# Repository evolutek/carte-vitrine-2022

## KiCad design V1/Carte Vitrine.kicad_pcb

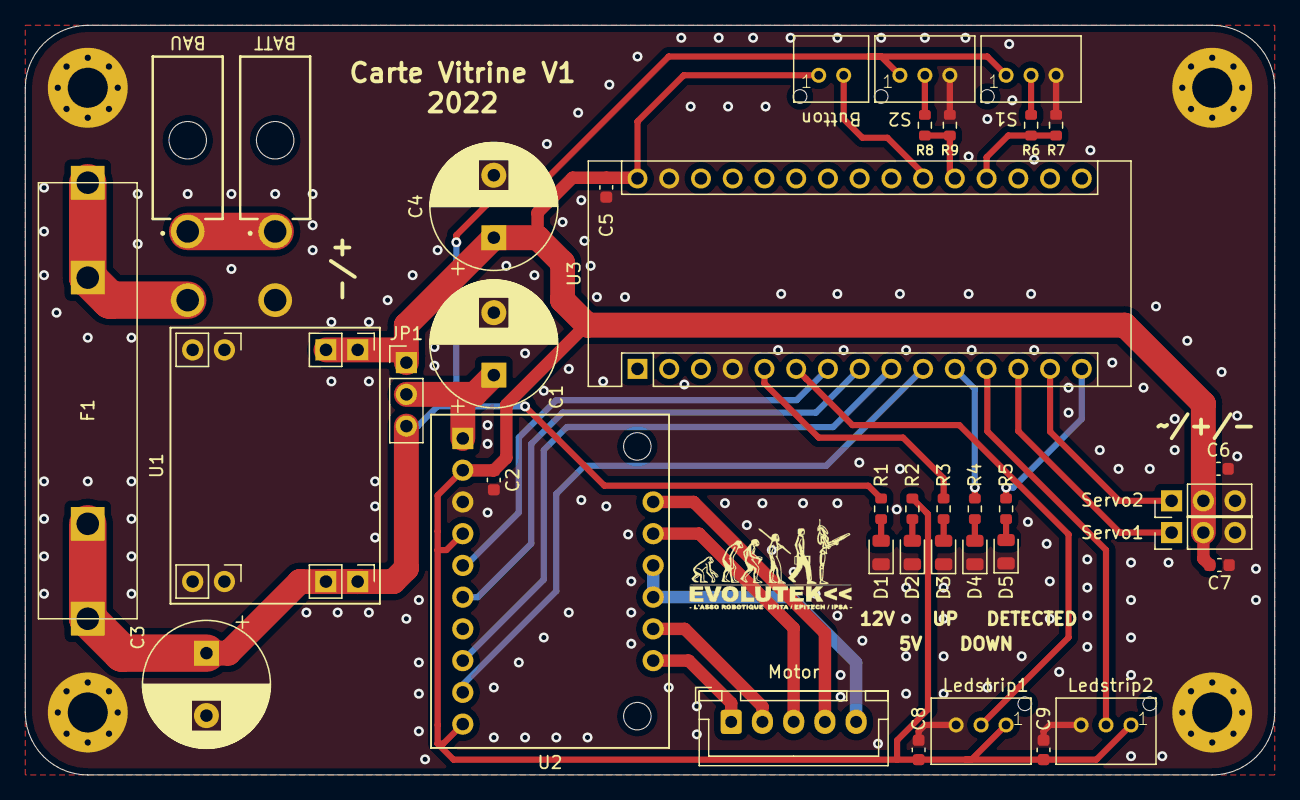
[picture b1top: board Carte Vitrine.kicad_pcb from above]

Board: 2 copper layers, 100.0 x 60.0 mm, 42 parts (0 on the bottom side), 32 nets.

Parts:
BATT: Conn_01x02_Male; 649002227222
BAU: Conn_01x02_Male; 649002227222
Button: Conn_01x02_Male; B02B-PASK
C1: 180uF; CP_Radial_D10.0mm_P5.00mm
C2, C5: 100nF; C_0603_1608Metric
C3: 470uF; CP_Radial_D10.0mm_P5.00mm
C4: 330uF; CP_Radial_D10.0mm_P5.00mm
C6, C7, C8, C9: 4.7uF; C_0603_1608Metric
D1, D2: Red; LED_0805_2012Metric
D3, D4, D5: Green; LED_0805_2012Metric
F1: Fuse; 8040-PORTE-FUSIBLE
H1, H2, H3, H4: MountingHole_Pad; MountingHole_3.2mm_M3_Pad_Via
JP1: Jumper_3_Open; PinHeader_1x03_P2.54mm_Vertical
Ledstrip1, Ledstrip2: Conn_01x03_Male; B03B-PASK
Motor: Conn_01x05_Male; JST_XH_B5B-XH-A_1x05_P2.50mm_Vertical
R1: 510; R_0603_1608Metric
R2, R3, R4, R5: 150; R_0603_1608Metric
R6, R8: 10k; R_0603_1608Metric
R7, R9: 4.7k; R_0603_1608Metric
S1, S2: Conn_01x03_Male; B03B-PASK
Servo1, Servo2: Conn_01x03_Male; PinHeader_1x03_P2.54mm_Vertical
U1: MP1584EB; MP1584EN
U2: TB6612FNG
U3: Arduino Nano; ArduinoNano

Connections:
+5V: Button.1, C2.2, C4.1, C5.1, C6.2, C7.2, C8.1, C9.1, JP1.1, Ledstrip1.1, Ledstrip2.1, R2.1, Servo1.2, Servo2.2, U1.3, U2.2, U2.4, U2.10, U3.30
+12V: C3.1, F1.2, JP1.3, R1.1, S1.1, S2.1, U1.1
AIN1: U2.8, U3.9
AIN2: U2.9, U3.10
BIN1: U2.6, U3.8
BIN2: U2.5, U3.7
BTN_MOVE: Button.2, U3.21
CAPTEUR_1: R6.2, R7.2, U3.19
CAPTEUR_2: R8.2, R9.2, U3.20
GND: BATT.2, C1.2, C2.1, C3.2, C4.2, C5.2, C6.1, C7.1, C8.2, C9.2, D1.1, D2.1, D3.1, D4.1, D5.1, H1.1, H2.1, H3.1, H4.1, Ledstrip1.3, Ledstrip2.3, R7.1, R9.1, S1.3, S2.3, Servo1.3, Servo2.3, U1.2, U1.4, U2.3, U3.4, U3.29
LEDSTRIP_1: Ledstrip1.2, U3.6
LEDSTRIP_2: Ledstrip2.2, U3.12
LED_DETECT: R5.1, U3.15
LED_DOWN: R4.1, U3.11
LED_UP: R3.1, U3.5
unnamed: BATT.1, BAU.1
unnamed: BAU.2, F1.1
unnamed: C1.1, JP1.2, U2.1
unnamed: D1.2, R1.2
unnamed: D2.2, R2.2
unnamed: D3.2, R3.2
unnamed: D4.2, R4.2
unnamed: D5.2, R5.2
unnamed: Motor.1, U2.16
unnamed: Motor.2, U2.15
unnamed: Motor.3, U2.12
unnamed: Motor.4, U2.11
unnamed: Motor.5, U2.13, U2.14
unnamed: R6.1, S1.2
unnamed: R8.1, S2.2
SERVO_LEFT: Servo2.1, U3.14
SERVO_RIGHT: Servo1.1, U3.13

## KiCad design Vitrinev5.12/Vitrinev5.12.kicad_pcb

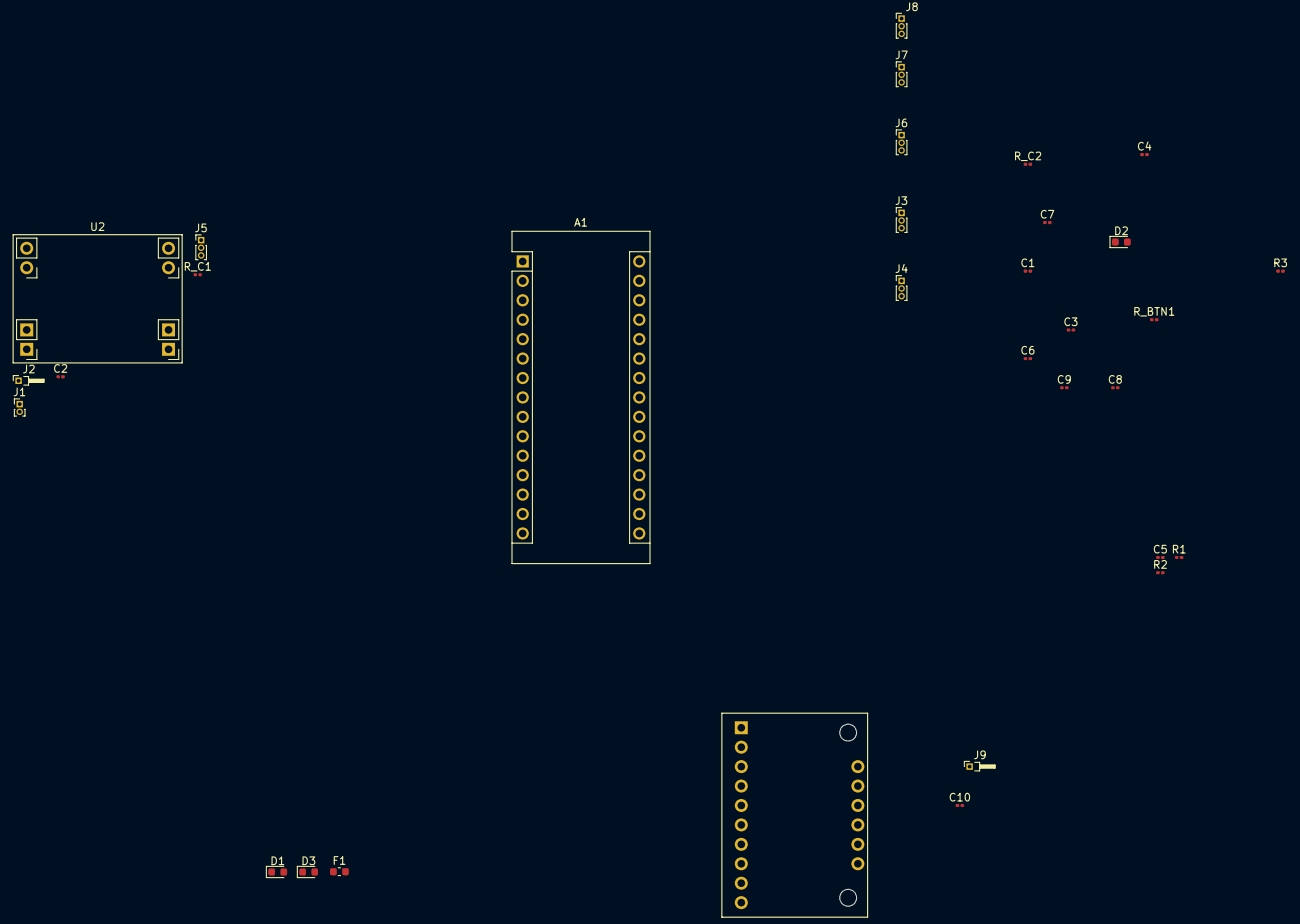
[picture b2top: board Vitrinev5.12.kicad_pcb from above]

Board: 2 copper layers, 32 parts (0 on the bottom side), 34 nets, no tracks yet.

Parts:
A1: Arduino; Arduino_Nano
C1, C2, C9, C10: C; C_0201_0603Metric
C3, C4: 1mF; C_0201_0603Metric
C5, C6, C7, C8: 100nF; C_0201_0603Metric
D1: Led_Up; LED_0603_1608Metric
D2: Led_Down; LED_0603_1608Metric
D3: Led_Detect; LED_0603_1608Metric
F1: Fuse; Fuse_0603_1608Metric
J1: BAU; PinHeader_1x02_P1.00mm_Vertical
J2: 12V; PinHeader_1x01_P1.00mm_Horizontal
J3: LedRing; PinHeader_1x03_P1.00mm_Vertical
J4: Capteur_2; PinHeader_1x03_P1.00mm_Vertical
J5: Capteur_1; PinHeader_1x03_P1.00mm_Vertical
J6: BTN_Move; PinHeader_1x03_P1.00mm_Vertical
J7: Servo_Left; PinHeader_1x03_P1.00mm_Vertical
J8: Servo_Right; PinHeader_1x03_P1.00mm_Vertical
J9: MA1; PinHeader_1x01_P1.00mm_Horizontal
R1, R2, R3: 220; R_0201_0603Metric
R_BTN1: 10K; R_0201_0603Metric
R_C1, R_C2: R; R_0201_0603Metric
U1: TB6612FNG
U2: MP1584EB; MP1584EN

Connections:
+5V: A1.27, J3.1, J6.1, J7.2, U1.2, U1.4, U1.10, U2.3
+12V: C1.1, C2.1, F1.2, J4.1, J5.1, U1.1, U2.1
AIN1: A1.13, U1.8
AIN2: A1.14, U1.9
BAU: J1.2, J2.1
BIN1: A1.12, U1.6
BIN2: A1.11, U1.5
BTN_MOVE: A1.7, J6.2
CAPTEUR_1: A1.19, J5.2
CAPTEUR_2: A1.20, J4.2
GND1: C1.2, C6.2, C7.2, C10.1
GND2: C3.1, C4.1, C5.2, C8.2, C9.2, D1.1, D2.1, D3.1, U2.4
LEDSTRIP: A1.21, J3.2
LED_DETECT: A1.10, R3.1
LED_DOWN: A1.9, R2.1
LED_UP: A1.8, R1.1
unnamed: A1.29, C9.1
unnamed: C2.2, U2.2
unnamed: C4.2, J7.3
unnamed: C5.1, R_BTN1.2
unnamed: C6.1, R_C1.2
unnamed: C7.1, R_C2.2
unnamed: C8.1, J3.3
unnamed: C10.2, U1.13
unnamed: D1.2, R1.2
unnamed: D2.2, R2.2
unnamed: D3.2, R3.2
unnamed: F1.1, J1.1
unnamed: J4.3, R_C2.1
unnamed: J5.3, R_C1.1
unnamed: J6.3, R_BTN1.1
unnamed: J9.1, U1.11
SERVO_LEFT: A1.6, J7.1
SERVO_RIGHT: A1.5, J8.1

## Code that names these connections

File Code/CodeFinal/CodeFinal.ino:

#include <Adafruit_NeoPixel.h>
#include <Servo.h>


// Pins definitions

#define PIN_LED_ONBOARD 12
#define PIN_LED_UP      2
#define PIN_LED_DOWN    8

#define PIN_MOTOR_A 6
#define PIN_MOTOR_B 7
#define PIN_MOTOR_C 5
#define PIN_MOTOR_D 4

#define PIN_SENSOR_LEFT  A0
#define PIN_SENSOR_RIGHT A1

#define PIN_BTN_MOVE A2

#define PIN_LEDSTRIP_INNER 3
#define PIN_LEDSTRIP_OUTER 9

#define PIN_SERVO_LEFT  11
#define PIN_SERVO_RIGHT 10


// Other parameters

#define STEPPER_SPEED 500
#define FADDING_COLOR 0x35FF00
#define FADDING_DELAY 50
#define TAKE_COLOR 0xFF0000
#define TAKE_BLINK_DELAY 500
#define TURN_COLOR 0xFFFFFF
#define TURN_DELAY 10
#define OK_COLOR 0x0000FF
#define OK_WAIT_DELAY 5000
#define OK_BLINK_DELAY 250


bool state = true; // True = mode attente, false = mode statuette
bool initialized = false; // Dit si l'état actuel est initialisé ou pas
Adafruit_NeoPixel ledStrip = Adafruit_NeoPixel(16, PIN_LEDSTRIP_INNER, NEO_RGB + NEO_KHZ800);
int brightness; // Fadding purpose
bool dir; // Savoir dans quelle direction faire varier la brightness
Servo right_servo;
Servo left_servo;
int led = 0; // Pour l'animation de rotation

const int stepper_pins[] = {PIN_MOTOR_A, PIN_MOTOR_B, PIN_MOTOR_C, PIN_MOTOR_D};
const bool stepper_steps[8][4] = {
    {HIGH, LOW , LOW , LOW },
    {HIGH, LOW , HIGH, LOW },
    {LOW , LOW , HIGH, LOW },
    {LOW , HIGH, HIGH, LOW },
    {LOW , HIGH, LOW , LOW },
    {LOW , HIGH, LOW , HIGH},
    {LOW , LOW , LOW , HIGH},
    {HIGH, LOW , LOW , HIGH}
};
int stepper_current_step = 0;


void stepper_write_step(const bool* states) {
    for (int i = 4; i--;)
        digitalWrite(stepper_pins[i], states[i]);
}

void stepper_write_all(bool state) {
    for (int i = 4; i--;)
        digitalWrite(stepper_pins[i], state);
}

  
void setup() {
  ledStrip.begin();
  ledStrip.setBrightness(255);

  right_servo.attach(PIN_SERVO_RIGHT);
  left_servo.attach(PIN_SERVO_LEFT);

  Serial.begin(115200);

  for (int i = 4; i-- > 0;)
    pinMode(stepper_pins[i], OUTPUT);
  stepper_write_all(LOW);
}


void loop() {
  if (state) {
    stepper_write_all(LOW);

    if (!initialized) {
      brightness = 10;
      dir = true;
      ledStrip.show();
      right_servo.write(20);
      left_servo.write(180-20);
      initialized = true;

      // On vérifie que la vitrine soit vide avant d'attendre qu'on la remplisse
      bool on = true;
      while (digitalRead(PIN_SENSOR_LEFT) == HIGH || digitalRead(PIN_SENSOR_RIGHT) == HIGH) {
        ledStrip.fill(on ? TAKE_COLOR : 0x000000, 0, 16);
        ledStrip.show();
        delay(TAKE_BLINK_DELAY);
        on = !on;
      }

      ledStrip.fill(FADDING_COLOR, 0, ledStrip.numPixels());
      
    } else {
      // Animation des LEDs
      ledStrip.setBrightness(brightness);
      
      if (dir) {
        brightness = brightness + 5;
        if (brightness >= 255) {
          dir = false;
        }
      } else {
        brightness = brightness - 5;
        if (brightness <= 5) {
          dir = true;
        }
      }

      ledStrip.show();

      // Détection du changement d'état
      if (digitalRead(PIN_SENSOR_LEFT) == HIGH || digitalRead(PIN_SENSOR_RIGHT) == HIGH) {
        initialized = false;
        state = false;
      }

      // Délai
      delay(FADDING_DELAY);
    }
  } else {
    if (!initialized) {
      stepper_write_all(LOW);

      int i = 0;
      ledStrip.setBrightness(255);
      bool on = true;
      while (i * OK_BLINK_DELAY <= OK_WAIT_DELAY)
      {
        ledStrip.fill(on ? OK_COLOR : 0x000000, 0, ledStrip.numPixels());
        ledStrip.show();
        delay(OK_BLINK_DELAY);
        i++;
        on = !on;
      }
      ledStrip.fill(0x000000, 0, ledStrip.numPixels());
      dir = true;
      ledStrip.show();
      right_servo.write(110);
      left_servo.write(180-110);
      initialized = true;
      
    } else {

      // Animation des LEDs
      ledStrip.setPixelColor(led, 0x000000);
      led = (led+1) % 16;
      ledStrip.setPixelColor(led, TURN_COLOR);

      ledStrip.show();

      // Animation du stepper
      stepper_write_step(stepper_steps[stepper_current_step]);
      stepper_current_step++;
      if (stepper_current_step >= 8)
        stepper_current_step = 0;

      // Détection du changement d'état
      if (digitalRead(PIN_BTN_MOVE) == HIGH || digitalRead(PIN_SENSOR_LEFT) == LOW && digitalRead(PIN_SENSOR_RIGHT) == LOW ) {
        initialized = false;
        state = true;
      }

      // Délai
      delay(TURN_DELAY);
    }
  }
}

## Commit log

2022-04-18 version moche
2022-04-19 Fix schematics and add Board
2022-04-19 Fix Front-Board.pdf and add zip
2022-04-25 Fix V1 of the board
2022-05-19 Create new_dir
2022-05-20 Add code
2022-05-20 Add drivers
2022-05-20 Functional drivers
2022-05-20 Make a better ServoDriver.h
2022-05-21 Add a README and set a default speed in ServoDriver
2022-05-21 Update README (list syntax problem)
2022-05-22 Add missing driver init call in mainSetup
2022-05-22 Fix typo in README
2022-05-22 Code Easy V1
2022-05-22 Rename code_Easy/Code_Easy.ino to code_easy (old)/Code_Easy.ino
2022-05-22 Rename Code/StepperTest/StepperTest.ino to Code/StepperTest (old)/StepperTest.ino
2022-05-22 FIN CODE VITRINE
    Finalisation du code de la vitrine (TESTÉ)
2022-05-25 Rename and change stepper managment in CodeFinal.ino
